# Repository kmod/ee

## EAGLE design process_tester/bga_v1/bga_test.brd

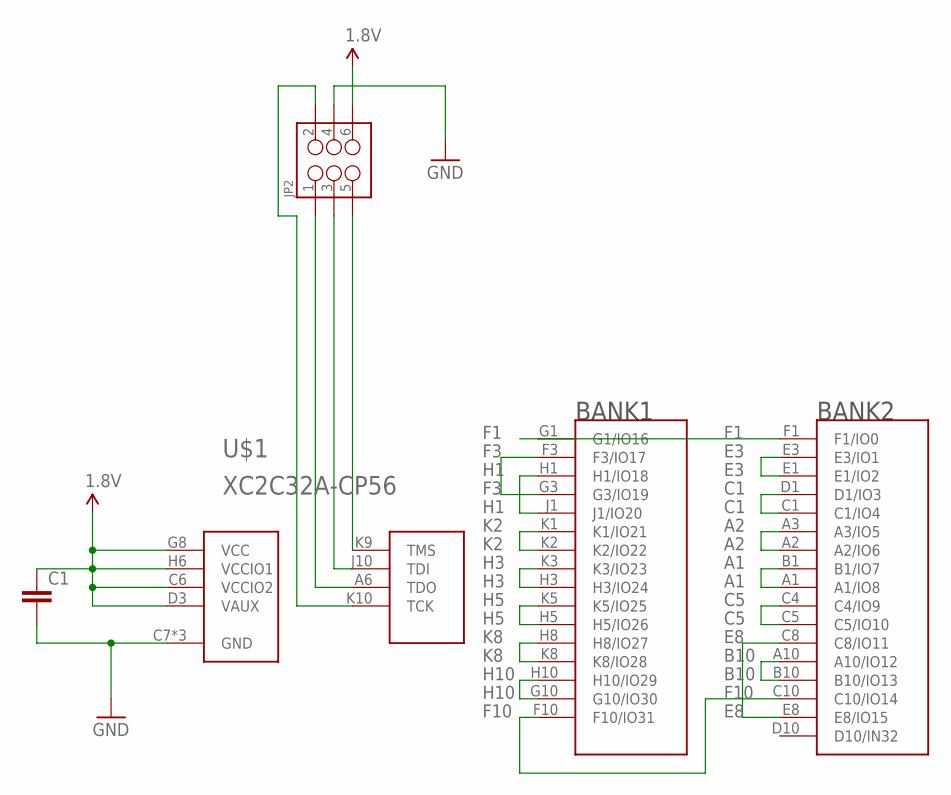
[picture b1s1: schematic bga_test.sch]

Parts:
C1: CAP0402-CAP; 0402-CAP
JP2: M03X2NO_SILK; 2X3-NS
U$1: XC2C32A-CP56; XILINX_CP56

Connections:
1.8V: C1.1, JP2.6, U$1.C6 (VCCIO2), U$1.D3 (VAUX), U$1.G8 (VCC), U$1.H6 (VCCIO1)
A1: U$1.A1 (A1/IO8), U$1.B1 (B1/IO7)
A2: U$1.A2 (A2/IO6), U$1.A3 (A3/IO5)
B10: U$1.A10 (A10/IO12), U$1.B10 (B10/IO13)
C1: U$1.C1 (C1/IO4), U$1.D1 (D1/IO3)
C5: U$1.C4 (C4/IO9), U$1.C5 (C5/IO10)
E3: U$1.E1 (E1/IO2), U$1.E3 (E3/IO1)
E8: U$1.C8 (C8/IO11), U$1.E8 (E8/IO15)
F1: U$1.F1 (F1/IO0), U$1.G1 (G1/IO16)
F3: U$1.F3 (F3/IO17), U$1.G3 (G3/IO19)
F10: U$1.C10 (C10/IO14), U$1.F10 (F10/IO31)
GND: C1.2, JP2.4, U$1.C7 (GND), U$1.F8 (GND), U$1.H4 (GND)
H1: U$1.H1 (H1/IO18), U$1.J1 (J1/IO20)
H3: U$1.H3 (H3/IO24), U$1.K3 (K3/IO23)
H5: U$1.H5 (H5/IO26), U$1.K5 (K5/IO25)
H10: U$1.G10 (G10/IO30), U$1.H10 (H10/IO29)
K2: U$1.K1 (K1/IO21), U$1.K2 (K2/IO22)
K8: U$1.H8 (H8/IO27), U$1.K8 (K8/IO28)
TCK: JP2.2, U$1.K10 (TCK)
TDI: JP2.3, U$1.J10 (TDI)
TDO: JP2.1, U$1.A6 (TDO)
TMS: JP2.5, U$1.K9 (TMS)

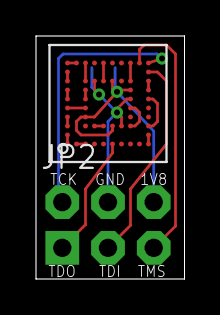
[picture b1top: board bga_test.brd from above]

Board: 2 copper layers, 8.2 x 13.5 mm, 3 parts (1 on the bottom side), 22 nets.

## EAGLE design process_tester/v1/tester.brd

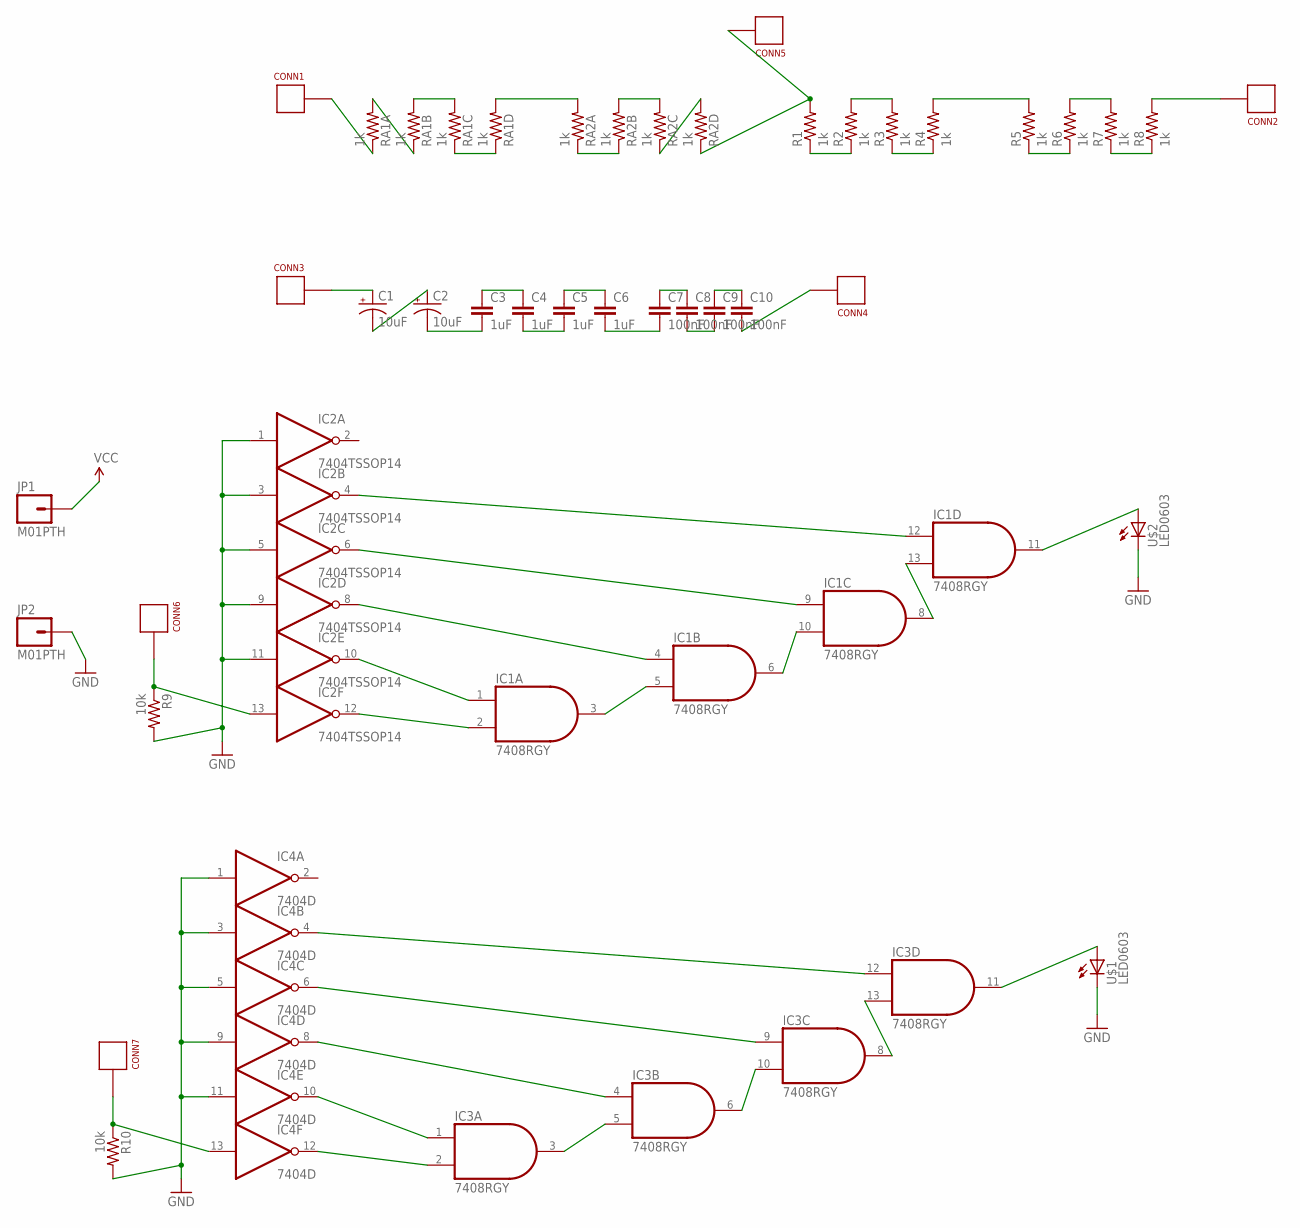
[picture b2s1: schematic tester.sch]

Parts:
C1, C2: 10uF; EIA3216
C3, C4, C5, C6: 1uF; 0805
C7, C8, C9, C10: 100nF; 0402-CAP
CONN1, CONN2, CONN3, CONN4, CONN5, CONN6, CONN7: CONNECTOR; TESTPAD
IC1, IC3: 7408RGY; QFN14
IC2: 7404TSSOP14; TSSOP14
IC4: 7404D; SO14
JP1, JP2: M01PTH; 1X01
R1, R2, R3, R4: 1k; 0603-RES
R5, R6, R7, R8: 1k; 0402-RES
R9, R10: 10k; 0402-RES
RA1, RA2: 1k; 0603-ARV
U$1, U$2: LED0603; 0603_LED

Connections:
GND: IC1.7 (GND), IC2.1 (I), IC2.3 (I), IC2.5 (I), IC2.7 (GND), IC2.9 (I), IC2.11 (I), IC3.7 (GND), IC4.1 (I), IC4.3 (I), IC4.5 (I), IC4.7 (GND), IC4.9 (I), IC4.11 (I), JP2.1, R9.2, R10.2, U$1.C, U$2.C
unnamed: RA1.2 (1), RA1.8 (2)
unnamed: CONN1.P, RA1.1
unnamed: RA1.6 (2), RA1.7 (2)
unnamed: RA1.3 (1), RA1.4 (1)
unnamed: RA1.5 (2), RA2.8 (2)
unnamed: RA2.1, RA2.2 (1)
unnamed: RA2.6 (2), RA2.7 (2)
unnamed: RA2.3 (1), RA2.5 (2)
unnamed: R1.1, R2.1
unnamed: R2.2, R3.2
unnamed: R3.1, R4.1
unnamed: R4.2, R5.2
unnamed: R5.1, R6.1
unnamed: R6.2, R7.2
unnamed: R7.1, R8.1
unnamed: CONN2.P, R8.2
unnamed: CONN5.P, R1.2, RA2.4 (1)
unnamed: C1.A (+), CONN3.P
unnamed: C1.C (-), C2.A (+)
unnamed: C2.C (-), C3.2
unnamed: C3.1, C4.1
unnamed: C4.2, C5.2
unnamed: C5.1, C6.1
unnamed: C6.2, C7.2
unnamed: C8.2, C9.2
unnamed: C9.1, C10.1
unnamed: C7.1, C8.1
unnamed: C10.2, CONN4.P
unnamed: IC1.2 (I1), IC2.12 (O)
unnamed: IC1.1 (I0), IC2.10 (O)
unnamed: IC1.4 (I0), IC2.8 (O)
unnamed: IC1.3 (O), IC1.5 (I1)
unnamed: IC1.6 (O), IC1.10 (I1)
unnamed: IC1.9 (I0), IC2.6 (O)
unnamed: IC1.12 (I0), IC2.4 (O)
unnamed: IC1.8 (O), IC1.13 (I1)
unnamed: IC1.11 (O), U$2.A
unnamed: IC3.3 (O), IC3.5 (I1)
unnamed: IC3.6 (O), IC3.10 (I1)
unnamed: IC3.8 (O), IC3.13 (I1)
unnamed: IC3.11 (O), U$1.A
unnamed: IC3.2 (I1), IC4.12 (O)
unnamed: IC3.1 (I0), IC4.10 (O)
unnamed: IC3.9 (I0), IC4.6 (O)
unnamed: IC3.4 (I0), IC4.8 (O)
unnamed: IC3.12 (I0), IC4.4 (O)
unnamed: CONN6.P, IC2.13 (I), R9.1
unnamed: CONN7.P, IC4.13 (I), R10.1
VCC: IC1.14 (VCC), IC2.14 (VCC), IC3.14 (VCC), IC4.14 (VCC), JP1.1

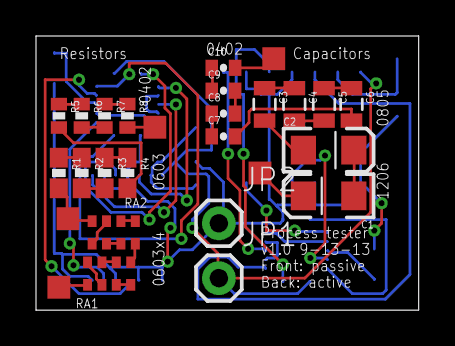
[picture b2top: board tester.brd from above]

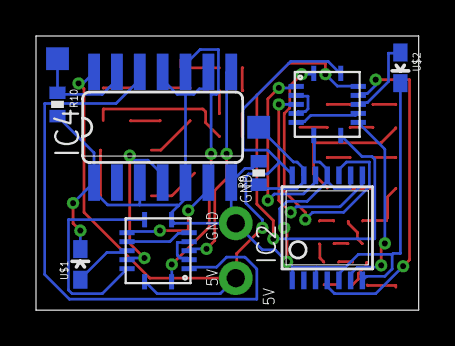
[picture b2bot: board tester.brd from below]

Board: 2 copper layers, 21.3 x 15.2 mm, 37 parts (10 on the bottom side), 50 nets.

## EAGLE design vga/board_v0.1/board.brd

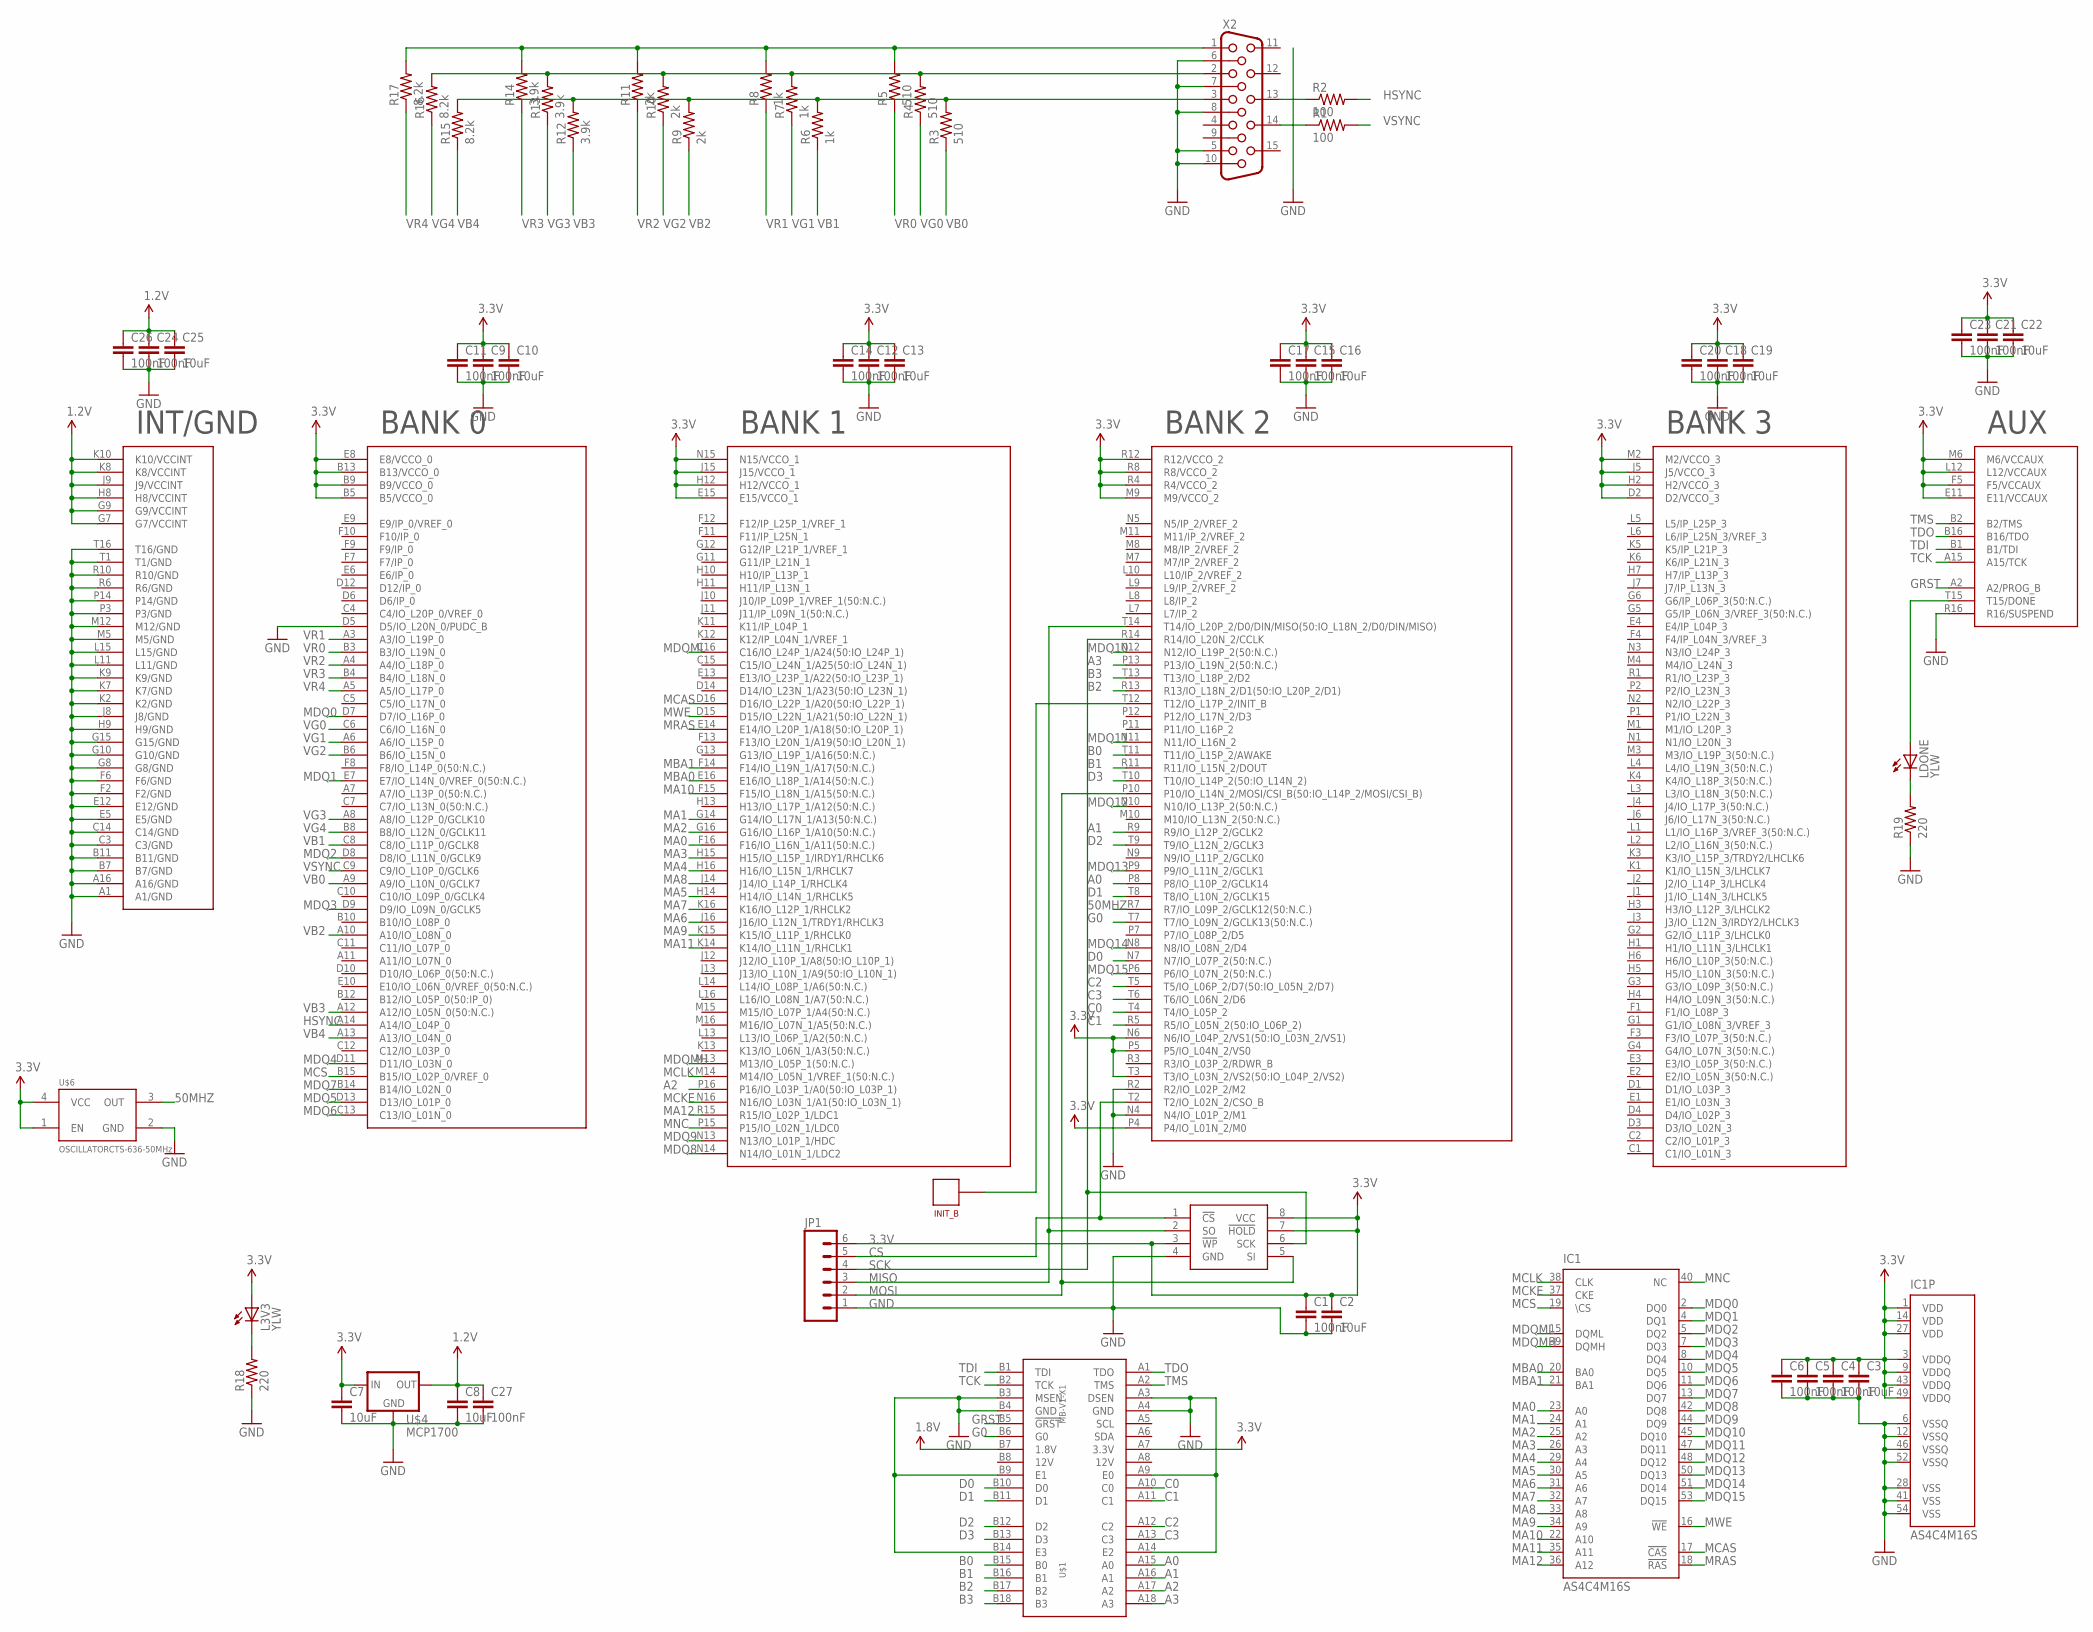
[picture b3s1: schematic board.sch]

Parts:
C1, C4, C5, C6, C9, C11, C12, C14, C15, C17, C18, C20, C21, C23, C24, C26, C27: 100nF; 0402-CAP
C2, C3, C7, C8, C10, C13, C16, C19, C22, C25: 10uF; 0805
IC1: AS4C4M16S; TSOP54-400
INIT_B: CONNECTOR1.27; TESTPAD-1.27
JP1: M06SIP; 1X06
L3V3: YLW; 0603_LED
LDONE: YLW; 0603_LED
R1, R2: 100; 0603-RES
R3, R4, R5: 510; 0603-RES
R6, R7, R8: 1k; 0603-RES
R9, R10, R11: 2k; 0603-RES
R12, R13, R14: 3.9k; 0603-RES
R15, R16, R17: 8.2k; 0603-RES
R18, R19: 220; 0603-RES
U$1: MB-V1-X1; PCIE-X1-EDGE
U$2: XC3S{50,100,200}A-FT256; XILINX_FT256
U$4: MCP1700; SOT23-3
U$6: OSCILLATORCTS-636-50MHz; CTS-636
U$7: S25FL; SO08
X2: HF15H; HDF15H

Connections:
1.2V: C8.1, C24.1, C25.1, C26.1, C27.1, U$2.G7 (G7/VCCINT), U$2.G9 (G9/VCCINT), U$2.H8 (H8/VCCINT), U$2.J9 (J9/VCCINT), U$2.K8 (K8/VCCINT), U$2.K10 (K10/VCCINT), U$4.2 (OUT)
1.8V: U$1.B7 (1.8V)
3.3V: C1.1, C2.1, C3.1, C4.1, C5.1, C6.1, C7.1, C9.1, C10.1, C11.1, C12.1, C13.1, C14.1, C15.1, C16.1, C17.1, C18.1, C19.1, C20.1, C21.1, C22.1, C23.1, IC1.1 (VDD), IC1.3 (VDDQ), IC1.9 (VDDQ), IC1.14 (VDD), IC1.27 (VDD), IC1.43 (VDDQ), IC1.49 (VDDQ), JP1.6, L3V3.A, U$1.A7 (3.3V), U$2.B5 (B5/VCCO_0), U$2.B9 (B9/VCCO_0), U$2.B13 (B13/VCCO_0), U$2.D2 (D2/VCCO_3), U$2.E8 (E8/VCCO_0), U$2.E11 (E11/VCCAUX), U$2.E15 (E15/VCCO_1), U$2.F5 (F5/VCCAUX), U$2.H2 (H2/VCCO_3), U$2.H12 (H12/VCCO_1), U$2.J5 (J5/VCCO_3), U$2.J15 (J15/VCCO_1), U$2.L12 (L12/VCCAUX), U$2.M2 (M2/VCCO_3), U$2.M6 (M6/VCCAUX), U$2.M9 (M9/VCCO_2), U$2.N6 (N6/IO_L04P_2/VS1(50:IO_L03N_2/VS1)), U$2.N15 (N15/VCCO_1), U$2.P4 (P4/IO_L01N_2/M0), U$2.P5 (P5/IO_L04N_2/VS0), U$2.R4 (R4/VCCO_2), U$2.R8 (R8/VCCO_2), U$2.R12 (R12/VCCO_2), U$2.T3 (T3/IO_L03N_2/VS2(50:IO_L04P_2/VS2)), U$4.3 (IN), U$6.1 (EN), U$6.4 (VCC), U$7.3 (!WP), U$7.7 (!HOLD), U$7.8 (VCC)
50MHZ: U$2.R7 (R7/IO_L09P_2/GCLK12(50:N.C.)), U$6.3 (OUT)
A0: U$1.A15 (A0), U$2.P8 (P8/IO_L10P_2/GCLK14)
A1: U$1.A16 (A1), U$2.R9 (R9/IO_L12P_2/GCLK2)
A2: U$1.A17 (A2), U$2.P16 (P16/IO_L03P_1/A0(50:IO_L03P_1))
A3: U$1.A18 (A3), U$2.P13 (P13/IO_L19N_2(50:N.C.))
B0: U$1.B15 (B0), U$2.T11 (T11/IO_L15P_2/AWAKE)
B1: U$1.B16 (B1), U$2.R11 (R11/IO_L15N_2/DOUT)
B2: U$1.B17 (B2), U$2.R13 (R13/IO_L18N_2/D1(50:IO_L20P_2/D1))
B3: U$1.B18 (B3), U$2.T13 (T13/IO_L18P_2/D2)
C0: U$1.A10 (C0), U$2.T4 (T4/IO_L05P_2)
C1: U$1.A11 (C1), U$2.R5 (R5/IO_L05N_2(50:IO_L06P_2))
C2: U$1.A12 (C2), U$2.T5 (T5/IO_L06P_2/D7(50:IO_L05N_2/D7))
C3: U$1.A13 (C3), U$2.T6 (T6/IO_L06N_2/D6)
CS: JP1.5, U$2.T2 (T2/IO_L02N_2/CSO_B), U$7.1 (!CS)
D0: U$1.B10 (D0), U$2.N7 (N7/IO_L07P_2(50:N.C.))
D1: U$1.B11 (D1), U$2.T8 (T8/IO_L10N_2/GCLK15)
D2: U$1.B12 (D2), U$2.T9 (T9/IO_L12N_2/GCLK3)
D3: U$1.B13 (D3), U$2.T10 (T10/IO_L14P_2(50:IO_L14N_2))
DONE: LDONE.A, U$2.T15 (T15/DONE)
G0: U$1.B6 (G0), U$2.T7 (T7/IO_L09N_2/GCLK13(50:N.C.))
GND: C1.2, C2.2, C3.2, C4.2, C5.2, C6.2, C7.2, C8.2, C9.2, C10.2, C11.2, C12.2, C13.2, C14.2, C15.2, C16.2, C17.2, C18.2, C19.2, C20.2, C21.2, C22.2, C23.2, C24.2, C25.2, C26.2, C27.2, IC1.6 (VSSQ), IC1.12 (VSSQ), IC1.28 (VSS), IC1.41 (VSS), IC1.46 (VSSQ), IC1.52 (VSSQ), IC1.54 (VSS), JP1.1, R18.1, R19.1, U$1.A3 (DSEN), U$1.A4 (GND), U$1.A9 (E0), U$1.A14 (E2), U$1.B3 (MSEN), U$1.B4 (GND), U$1.B9 (E1), U$1.B14 (E3), U$2.A1 (A1/GND), U$2.A16 (A16/GND), U$2.B7 (B7/GND), U$2.B11 (B11/GND), U$2.C3 (C3/GND), U$2.C14 (C14/GND), U$2.D5 (D5/IO_L20N_0/PUDC_B), U$2.E5 (E5/GND), U$2.E12 (E12/GND), U$2.F2 (F2/GND), U$2.F6 (F6/GND), U$2.G8 (G8/GND), U$2.G10 (G10/GND), U$2.G15 (G15/GND), U$2.H9 (H9/GND), U$2.J8 (J8/GND), U$2.K2 (K2/GND), U$2.K7 (K7/GND), U$2.K9 (K9/GND), U$2.L11 (L11/GND), U$2.L15 (L15/GND), U$2.M5 (M5/GND), U$2.M12 (M12/GND), U$2.N4 (N4/IO_L01P_2/M1), U$2.P3 (P3/GND), U$2.P14 (P14/GND), U$2.R2 (R2/IO_L02P_2/M2), U$2.R6 (R6/GND), U$2.R10 (R10/GND), U$2.R16 (R16/SUSPEND), U$2.T1 (T1/GND), U$2.T16 (T16/GND), U$4.1 (GND), U$6.2 (GND), U$7.4 (GND), X2.5, X2.6, X2.7, X2.8, X2.10
GRST: U$1.B5 (!GRST), U$2.A2 (A2/PROG_B)
HSYNC: R2.2, U$2.A14 (A14/IO_L04P_0)
MA0: IC1.23 (A0), U$2.F16 (F16/IO_L16N_1/A11(50:N.C.))
MA1: IC1.24 (A1), U$2.G14 (G14/IO_L17N_1/A13(50:N.C.))
MA2: IC1.25 (A2), U$2.G16 (G16/IO_L16P_1/A10(50:N.C.))
MA3: IC1.26 (A3), U$2.H15 (H15/IO_L15P_1/IRDY1/RHCLK6)
MA4: IC1.29 (A4), U$2.H16 (H16/IO_L15N_1/RHCLK7)
MA5: IC1.30 (A5), U$2.H14 (H14/IO_L14N_1/RHCLK5)
MA6: IC1.31 (A6), U$2.J16 (J16/IO_L12N_1/TRDY1/RHCLK3)
MA7: IC1.32 (A7), U$2.K16 (K16/IO_L12P_1/RHCLK2)
MA8: IC1.33 (A8), U$2.J14 (J14/IO_L14P_1/RHCLK4)
MA9: IC1.34 (A9), U$2.K15 (K15/IO_L11P_1/RHCLK0)
MA10: IC1.22 (A10), U$2.F15 (F15/IO_L18N_1/A15(50:N.C.))
MA11: IC1.35 (A11), U$2.K14 (K14/IO_L11N_1/RHCLK1)
MA12: IC1.36 (A12), U$2.R15 (R15/IO_L02P_1/LDC1)
MBA0: IC1.20 (BA0), U$2.E16 (E16/IO_L18P_1/A14(50:N.C.))
MBA1: IC1.21 (BA1), U$2.F14 (F14/IO_L19N_1/A17(50:N.C.))
MCAS: IC1.17 (!CAS), U$2.D16 (D16/IO_L22P_1/A20(50:IO_L22P_1))
MCKE: IC1.37 (CKE), U$2.N16 (N16/IO_L03N_1/A1(50:IO_L03N_1))
MCLK: IC1.38 (CLK), U$2.M14 (M14/IO_L05N_1/VREF_1(50:N.C.))
MCS: IC1.19 (\CS), U$2.B15 (B15/IO_L02P_0/VREF_0)
MDQ0: IC1.2 (DQ0), U$2.D7 (D7/IO_L16P_0)
MDQ1: IC1.4 (DQ1), U$2.E7 (E7/IO_L14N_0/VREF_0(50:N.C.))
MDQ2: IC1.5 (DQ2), U$2.D8 (D8/IO_L11N_0/GCLK9)
MDQ3: IC1.7 (DQ3), U$2.D9 (D9/IO_L09N_0/GCLK5)
MDQ4: IC1.8 (DQ4), U$2.D11 (D11/IO_L03N_0)
MDQ5: IC1.10 (DQ5), U$2.D13 (D13/IO_L01P_0)
MDQ6: IC1.11 (DQ6), U$2.C13 (C13/IO_L01N_0)
MDQ7: IC1.13 (DQ7), U$2.B14 (B14/IO_L02N_0)
MDQ8: IC1.42 (DQ8), U$2.N14 (N14/IO_L01N_1/LDC2)
MDQ9: IC1.44 (DQ9), U$2.N13 (N13/IO_L01P_1/HDC)
MDQ10: IC1.45 (DQ10), U$2.N12 (N12/IO_L19P_2(50:N.C.))
MDQ11: IC1.47 (DQ11), U$2.N11 (N11/IO_L16N_2)
MDQ12: IC1.48 (DQ12), U$2.N10 (N10/IO_L13P_2(50:N.C.))
MDQ13: IC1.50 (DQ13), U$2.P9 (P9/IO_L11N_2/GCLK1)
MDQ14: IC1.51 (DQ14), U$2.N8 (N8/IO_L08N_2/D4)
MDQ15: IC1.53 (DQ15), U$2.P6 (P6/IO_L07N_2(50:N.C.))
MDQMH: IC1.39 (DQMH), U$2.M13 (M13/IO_L05P_1(50:N.C.))
MDQML: IC1.15 (DQML), U$2.C16 (C16/IO_L24P_1/A24(50:IO_L24P_1))
MISO: JP1.3, U$2.T14 (T14/IO_L20P_2/D0/DIN/MISO(50:IO_L18N_2/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), U$7.2 (SO)
MNC: IC1.40 (NC), U$2.P15 (P15/IO_L02N_1/LDC0)
MOSI: JP1.2, U$2.P10 (P10/IO_L14N_2/MOSI/CSI_B(50:IO_L14P_2/M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), U$7.5 (SI)
MRAS: IC1.18 (!RAS), U$2.E14 (E14/IO_L20P_1/A18(50:IO_L20P_1))
MWE: IC1.16 (!WE), U$2.D15 (D15/IO_L22N_1/A21(50:IO_L22N_1))
unnamed: R1.1, X2.14
unnamed: R2.1, X2.13
unnamed: LDONE.C, R19.2
unnamed: INIT_B.P, U$2.T12 (T12/IO_L17P_2/INIT_B)
unnamed: R3.2, R6.2, R9.2, R12.2, R15.2, X2.3
unnamed: L3V3.C, R18.2
unnamed: R4.2, R7.2, R10.2, R13.2, R16.2, X2.2
unnamed: R5.2, R8.2, R11.2, R14.2, R17.2, X2.1
SCK: JP1.4, U$2.R14 (R14/IO_L20N_2/CCLK), U$7.6 (SCK)
TCK: U$1.B2 (TCK), U$2.A15 (A15/TCK)
TDI: U$1.B1 (TDI), U$2.B1 (B1/TDI)
TDO: U$1.A1 (TDO), U$2.B16 (B16/TDO)
TMS: U$1.A2 (TMS), U$2.B2 (B2/TMS)
VB0: R3.1, U$2.A9 (A9/IO_L10N_0/GCLK7)
VB1: R6.1, U$2.C8 (C8/IO_L11P_0/GCLK8)
VB2: R9.1, U$2.A10 (A10/IO_L08N_0)
VB3: R12.1, U$2.A12 (A12/IO_L05N_0(50:N.C.))
VB4: R15.1, U$2.A13 (A13/IO_L04N_0)
VG0: R4.1, U$2.C6 (C6/IO_L16N_0)
VG1: R7.1, U$2.A6 (A6/IO_L15P_0)
VG2: R10.1, U$2.B6 (B6/IO_L15N_0)
VG3: R13.1, U$2.A8 (A8/IO_L12P_0/GCLK10)
VG4: R16.1, U$2.B8 (B8/IO_L12N_0/GCLK11)
VR0: R5.1, U$2.B3 (B3/IO_L19N_0)
VR1: R8.1, U$2.A3 (A3/IO_L19P_0)
VR2: R11.1, U$2.A4 (A4/IO_L18P_0)
VR3: R14.1, U$2.B4 (B4/IO_L18N_0)
VR4: R17.1, U$2.A5 (A5/IO_L17P_0)
VSYNC: R1.2, U$2.C9 (C9/IO_L10P_0/GCLK6)

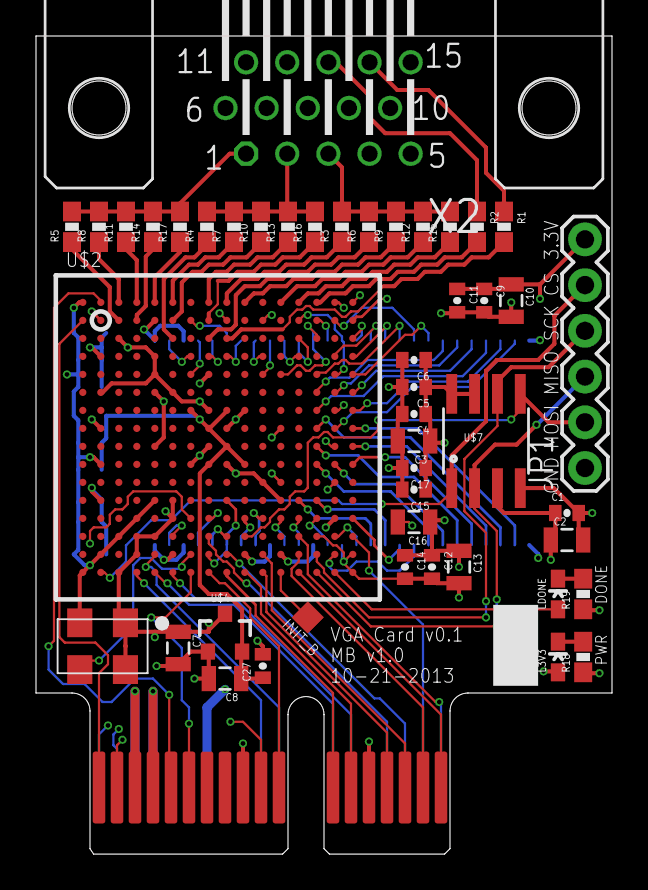
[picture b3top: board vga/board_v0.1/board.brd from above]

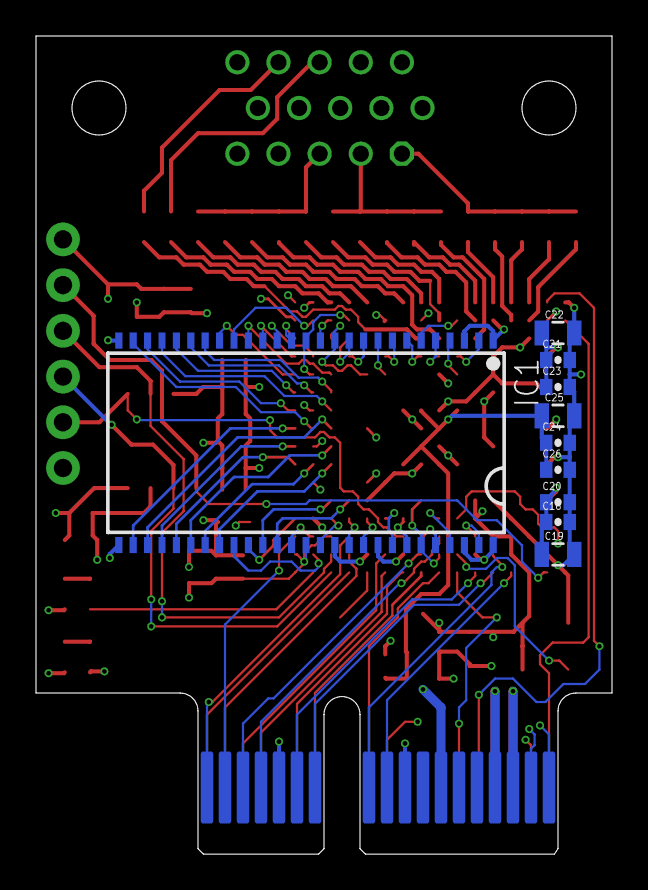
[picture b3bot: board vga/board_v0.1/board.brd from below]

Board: 4 copper layers, 32.0 x 45.5 mm, 57 parts (10 on the bottom side), 96 nets.

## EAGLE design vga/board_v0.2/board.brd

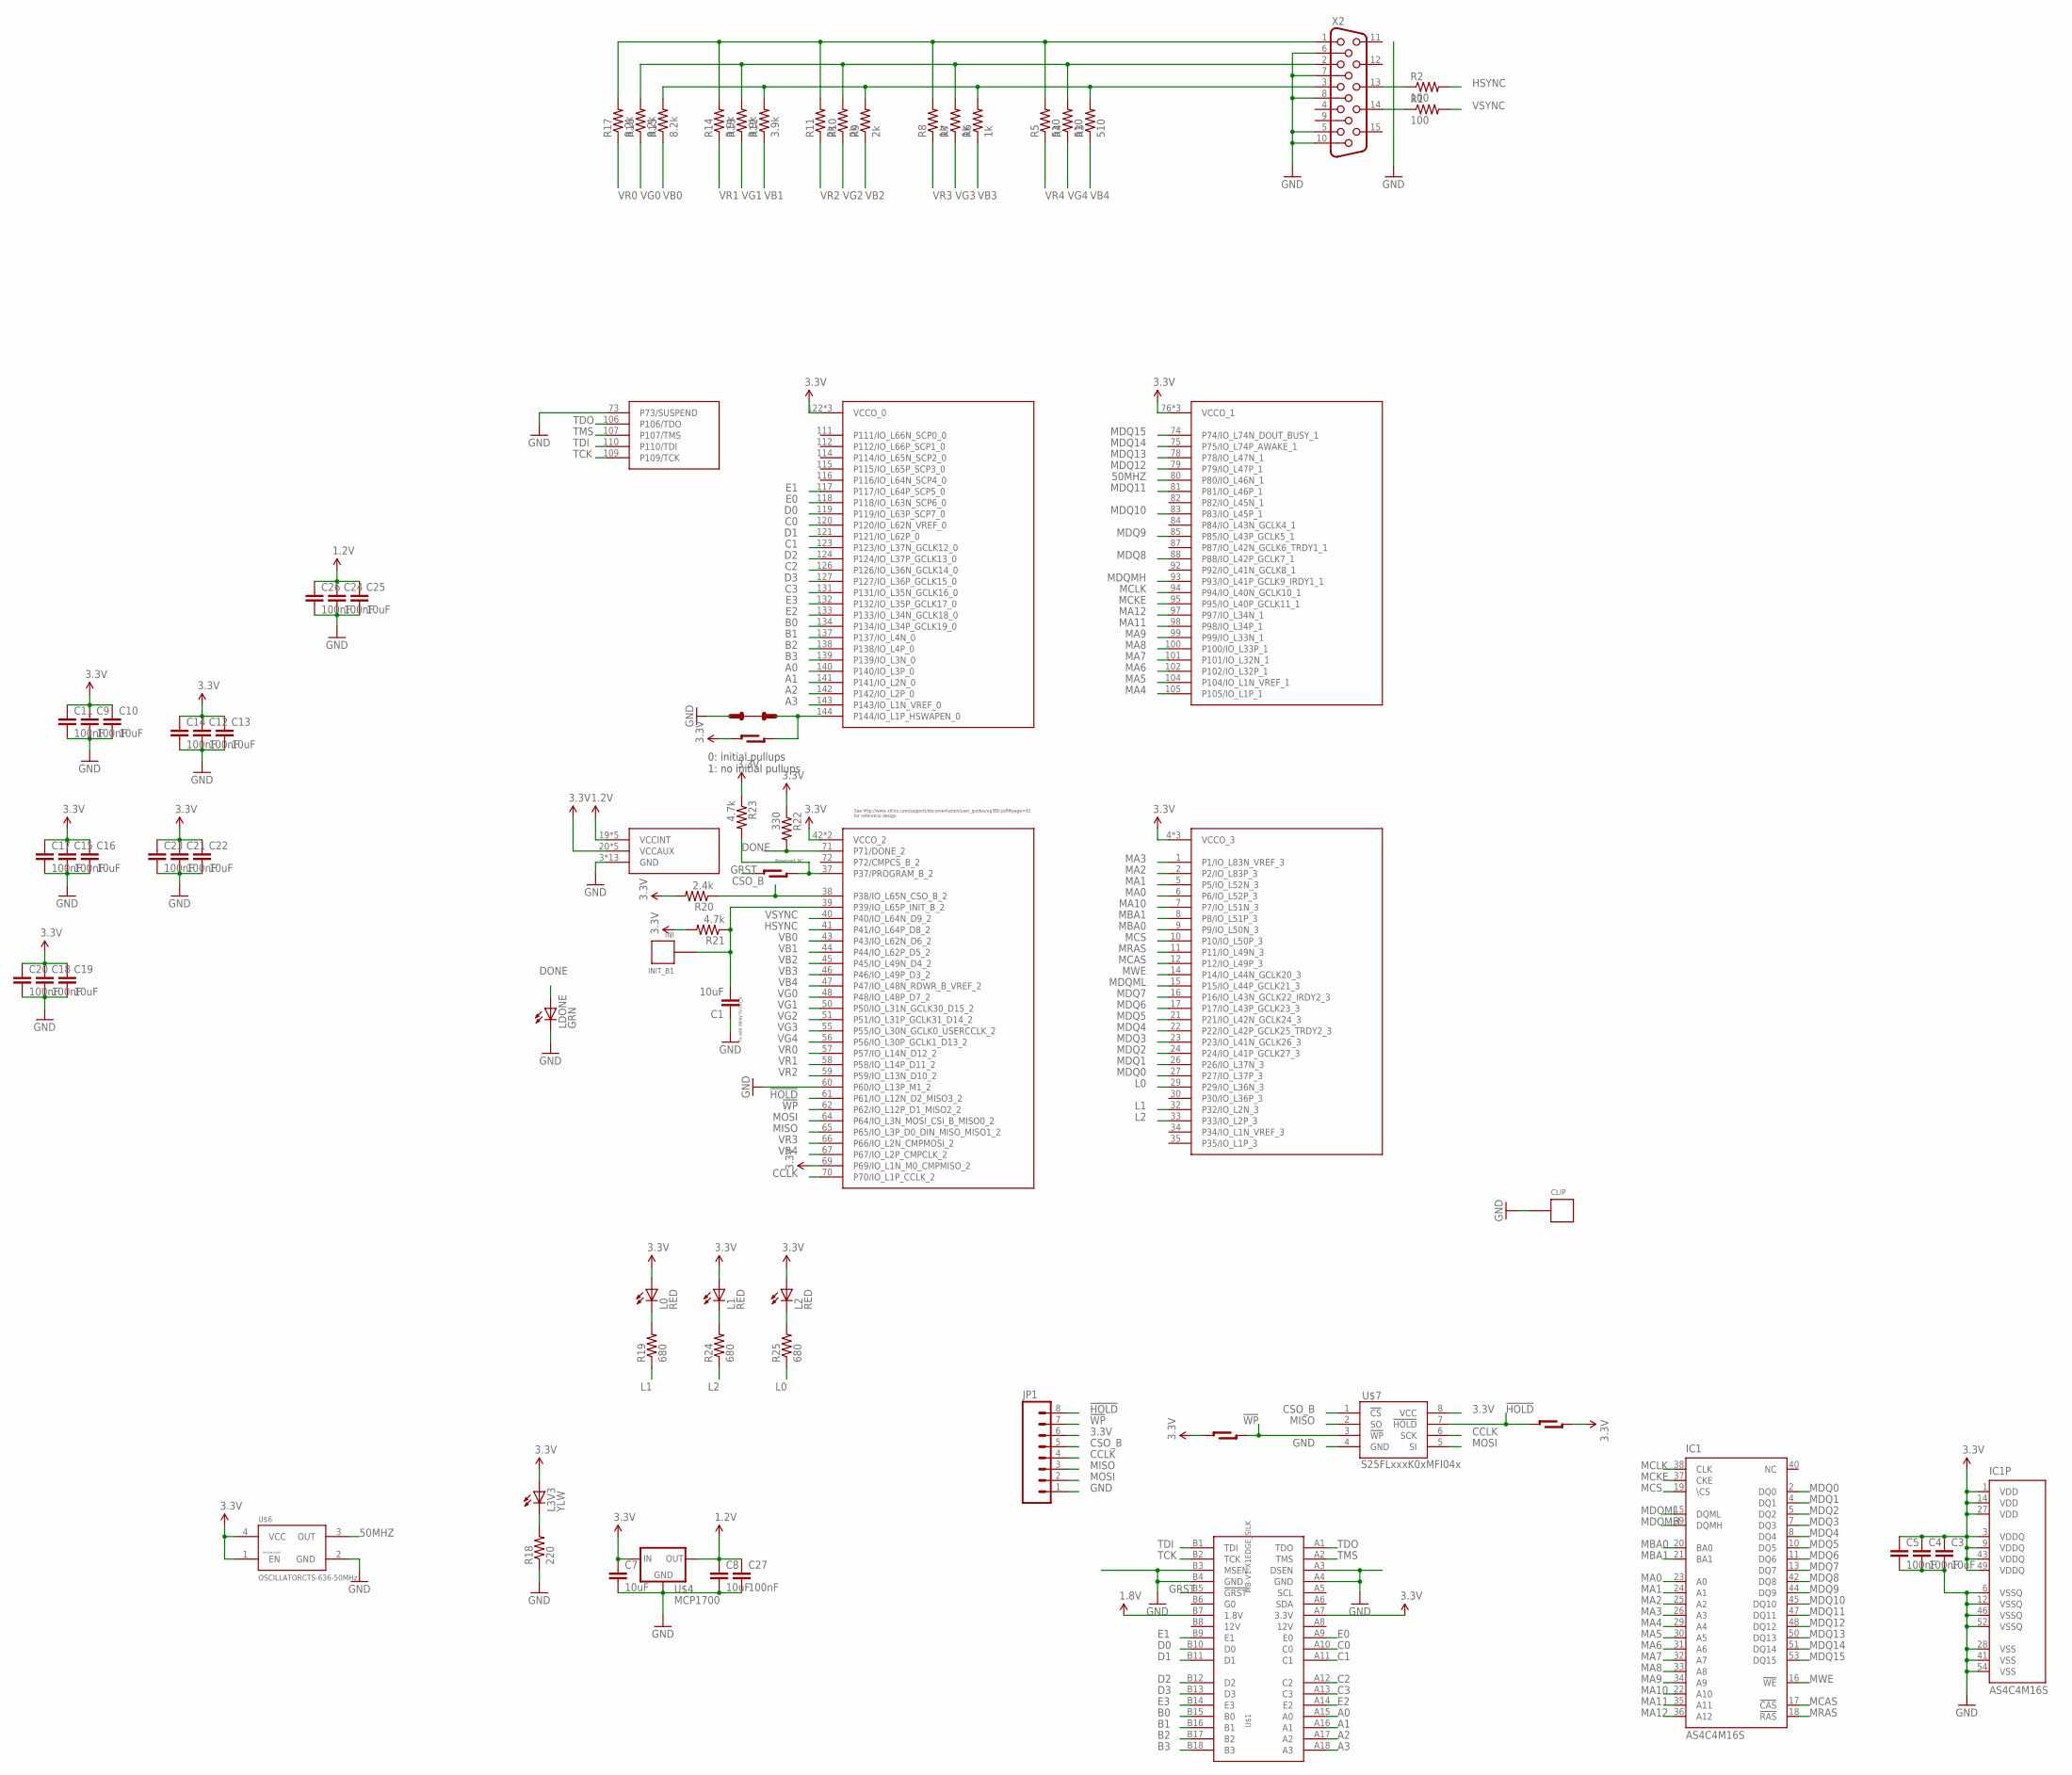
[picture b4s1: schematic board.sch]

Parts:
C1, C3, C7, C8, C10, C13, C16, C19, C22, C25: 10uF; 0805
C4, C5, C9, C11, C12, C14, C15, C17, C18, C20, C21, C23, C24, C26, C27: 100nF; 0402-CAP
CLIP: CONNECTORCLIP; CLIP-AREA
IC1: AS4C4M16S; TSOP54-400
INIT_B1: INI; TESTPAD-1.27
JP1: M08LOCK; 1X08_LOCK
L0, L1, L2: RED; 0603_LED
L3V3: YLW; 0603_LED
LDONE: GRN; 0603_LED
R1, R2: 100; 0603-RES
R3, R4, R5: 510; 0603-RES
R6, R7, R8: 1k; 0603-RES
R9, R10, R11: 2k; 0603-RES
R12, R13, R14: 3.9k; 0603-RES
R15, R16, R17: 8.2k; 0603-RES
R18: 220; 0603-RES
R19, R24, R25: 680; 0603-RES
R20: 2.4k; 0603-RES
R21, R23: 4.7k; 0603-RES
R22: 330; 0603-RES
SB1, SB3, SB4, SB5: SOLDER-BRIDGEOPEN; SOLDER-BRIDGE-OPEN
SB2: TRACE-CUT
U$1: MB-V1-X1EDGE_SILK; MB-V1-X1-EDGE
U$4: MCP1700; SOT23-3
U$6: OSCILLATORCTS-636-50MHz; CTS-636
U$7: S25FLxxxK0xMFI04x; SO08
U$9: XC6SLX-TQ144; XILINX_TQ144
X2: HF15H; HDF15H

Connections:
1.2V: C8.1, C24.1, C25.1, C26.1, C27.1, U$4.2 (OUT), U$9.19 (VCCINT), U$9.28 (VCCINT), U$9.52 (VCCINT), U$9.89 (VCCINT), U$9.128 (VCCINT)
1.8V: U$1.B7 (1.8V)
3.3V: C3.1, C4.1, C5.1, C7.1, C9.1, C10.1, C11.1, C12.1, C13.1, C14.1, C15.1, C16.1, C17.1, C18.1, C19.1, C20.1, C21.1, C22.1, C23.1, IC1.1 (VDD), IC1.3 (VDDQ), IC1.9 (VDDQ), IC1.14 (VDD), IC1.27 (VDD), IC1.43 (VDDQ), IC1.49 (VDDQ), JP1.6, L0.A, L1.A, L2.A, L3V3.A, R20.2, R21.2, R22.1, R23.1, SB1.R1, SB1.R2, SB3.L1, SB3.L2, SB4.R1, SB4.R2, U$1.A7 (3.3V), U$4.3 (IN), U$6.1 (EN), U$6.4 (VCC), U$7.8 (VCC), U$9.4 (VCCO_3), U$9.18 (VCCO_3), U$9.20 (VCCAUX), U$9.31 (VCCO_3), U$9.36 (VCCAUX), U$9.42 (VCCO_2), U$9.53 (VCCAUX), U$9.63 (VCCO_2), U$9.69 (P69/IO_L1N_M0_CMPMISO_2), U$9.76 (VCCO_1), U$9.86 (VCCO_1), U$9.90 (VCCAUX), U$9.103 (VCCO_1), U$9.122 (VCCO_0), U$9.125 (VCCO_0), U$9.129 (VCCAUX), U$9.135 (VCCO_0)
50MHZ: U$6.3 (OUT), U$9.80 (P80/IO_L46N_1)
!HOLD: JP1.8, SB3.R1, SB3.R2, U$7.7 (!HOLD), U$9.61 (P61/IO_L12N_D2_MISO3_2)
!WP: JP1.7, SB4.L1, SB4.L2, U$7.3 (!WP), U$9.62 (P62/IO_L12P_D1_MISO2_2)
A0: U$1.A15 (A0), U$9.140 (P140/IO_L3P_0)
A1: U$1.A16 (A1), U$9.141 (P141/IO_L2N_0)
A2: U$1.A17 (A2), U$9.142 (P142/IO_L2P_0)
A3: U$1.A18 (A3), U$9.143 (P143/IO_L1N_VREF_0)
B0: U$1.B15 (B0), U$9.134 (P134/IO_L34P_GCLK19_0)
B1: U$1.B16 (B1), U$9.137 (P137/IO_L4N_0)
B2: U$1.B17 (B2), U$9.138 (P138/IO_L4P_0)
B3: U$1.B18 (B3), U$9.139 (P139/IO_L3N_0)
C0: U$1.A10 (C0), U$9.120 (P120/IO_L62N_VREF_0)
C1: U$1.A11 (C1), U$9.123 (P123/IO_L37N_GCLK12_0)
C2: U$1.A12 (C2), U$9.126 (P126/IO_L36N_GCLK14_0)
C3: U$1.A13 (C3), U$9.131 (P131/IO_L35N_GCLK16_0)
CCLK: JP1.4, U$7.6 (SCK), U$9.70 (P70/IO_L1P_CCLK_2)
CSO_B: JP1.5, R20.1, U$7.1 (!CS), U$9.38 (P38/IO_L65N_CSO_B_2)
D0: U$1.B10 (D0), U$9.119 (P119/IO_L63P_SCP7_0)
D1: U$1.B11 (D1), U$9.121 (P121/IO_L62P_0)
D2: U$1.B12 (D2), U$9.124 (P124/IO_L37P_GCLK13_0)
D3: U$1.B13 (D3), U$9.127 (P127/IO_L36P_GCLK15_0)
DONE: LDONE.A, R22.2, U$9.71 (P71/DONE_2)
E0: U$1.A9 (E0), U$9.118 (P118/IO_L63N_SCP6_0)
E1: U$1.B9 (E1), U$9.117 (P117/IO_L64P_SCP5_0)
E2: U$1.A14 (E2), U$9.133 (P133/IO_L34N_GCLK18_0)
E3: U$1.B14 (E3), U$9.132 (P132/IO_L35P_GCLK17_0)
GND: C1.1, C3.2, C4.2, C5.2, C7.2, C8.2, C9.2, C10.2, C11.2, C12.2, C13.2, C14.2, C15.2, C16.2, C17.2, C18.2, C19.2, C20.2, C21.2, C22.2, C23.2, C24.2, C25.2, C26.2, C27.2, CLIP.P$1, CLIP.P$2, IC1.6 (VSSQ), IC1.12 (VSSQ), IC1.28 (VSS), IC1.41 (VSS), IC1.46 (VSSQ), IC1.52 (VSSQ), IC1.54 (VSS), JP1.1, LDONE.C, R18.1, SB2.L1, U$1.A3 (DSEN), U$1.A4 (GND), U$1.B3 (MSEN), U$1.B4 (GND), U$4.1 (GND), U$6.2 (GND), U$7.4 (GND), U$9.3 (GND), U$9.13 (GND), U$9.25 (GND), U$9.49 (GND), U$9.54 (GND), U$9.60 (P60/IO_L13P_M1_2), U$9.68 (GND), U$9.73 (P73/SUSPEND), U$9.77 (GND), U$9.91 (GND), U$9.96 (GND), U$9.108 (GND), U$9.113 (GND), U$9.130 (GND), U$9.136 (GND), X2.5, X2.6, X2.7, X2.8, X2.10
GRST: SB5.L1, SB5.L2, U$1.B5 (!GRST)
HSWAPEN: SB1.L1, SB1.L2, SB2.R1, U$9.144 (P144/IO_L1P_HSWAPEN_0)
HSYNC: R2.2, U$9.41 (P41/IO_L64P_D8_2)
INIT_B: C1.2, INIT_B1.P, R21.1, U$9.39 (P39/IO_L65P_INIT_B_2)
L0: R25.1, U$9.29 (P29/IO_L36N_3)
L1: R19.1, U$9.32 (P32/IO_L2N_3)
L2: R24.1, U$9.33 (P33/IO_L2P_3)
MA0: IC1.23 (A0), U$9.6 (P6/IO_L52P_3)
MA1: IC1.24 (A1), U$9.5 (P5/IO_L52N_3)
MA2: IC1.25 (A2), U$9.2 (P2/IO_L83P_3)
MA3: IC1.26 (A3), U$9.1 (P1/IO_L83N_VREF_3)
MA4: IC1.29 (A4), U$9.105 (P105/IO_L1P_1)
MA5: IC1.30 (A5), U$9.104 (P104/IO_L1N_VREF_1)
MA6: IC1.31 (A6), U$9.102 (P102/IO_L32P_1)
MA7: IC1.32 (A7), U$9.101 (P101/IO_L32N_1)
MA8: IC1.33 (A8), U$9.100 (P100/IO_L33P_1)
MA9: IC1.34 (A9), U$9.99 (P99/IO_L33N_1)
MA10: IC1.22 (A10), U$9.7 (P7/IO_L51N_3)
MA11: IC1.35 (A11), U$9.98 (P98/IO_L34P_1)
MA12: IC1.36 (A12), U$9.97 (P97/IO_L34N_1)
MBA0: IC1.20 (BA0), U$9.9 (P9/IO_L50N_3)
MBA1: IC1.21 (BA1), U$9.8 (P8/IO_L51P_3)
MCAS: IC1.17 (!CAS), U$9.12 (P12/IO_L49P_3)
MCKE: IC1.37 (CKE), U$9.95 (P95/IO_L40P_GCLK11_1)
MCLK: IC1.38 (CLK), U$9.94 (P94/IO_L40N_GCLK10_1)
MCS: IC1.19 (\CS), U$9.10 (P10/IO_L50P_3)
MDQ0: IC1.2 (DQ0), U$9.27 (P27/IO_L37P_3)
MDQ1: IC1.4 (DQ1), U$9.26 (P26/IO_L37N_3)
MDQ2: IC1.5 (DQ2), U$9.24 (P24/IO_L41P_GCLK27_3)
MDQ3: IC1.7 (DQ3), U$9.23 (P23/IO_L41N_GCLK26_3)
MDQ4: IC1.8 (DQ4), U$9.22 (P22/IO_L42P_GCLK25_TRDY2_3)
MDQ5: IC1.10 (DQ5), U$9.21 (P21/IO_L42N_GCLK24_3)
MDQ6: IC1.11 (DQ6), U$9.17 (P17/IO_L43P_GCLK23_3)
MDQ7: IC1.13 (DQ7), U$9.16 (P16/IO_L43N_GCLK22_IRDY2_3)
MDQ8: IC1.42 (DQ8), U$9.88 (P88/IO_L42P_GCLK7_1)
MDQ9: IC1.44 (DQ9), U$9.85 (P85/IO_L43P_GCLK5_1)
MDQ10: IC1.45 (DQ10), U$9.83 (P83/IO_L45P_1)
MDQ11: IC1.47 (DQ11), U$9.81 (P81/IO_L46P_1)
MDQ12: IC1.48 (DQ12), U$9.79 (P79/IO_L47P_1)
MDQ13: IC1.50 (DQ13), U$9.78 (P78/IO_L47N_1)
MDQ14: IC1.51 (DQ14), U$9.75 (P75/IO_L74P_AWAKE_1)
MDQ15: IC1.53 (DQ15), U$9.74 (P74/IO_L74N_DOUT_BUSY_1)
MDQMH: IC1.39 (DQMH), U$9.93 (P93/IO_L41P_GCLK9_IRDY1_1)
MDQML: IC1.15 (DQML), U$9.15 (P15/IO_L44P_GCLK21_3)
MISO: JP1.3, U$7.2 (SO), U$9.65 (P65/IO_L3P_D0_DIN_MISO_MISO1_2)
MOSI: JP1.2, U$7.5 (SI), U$9.64 (P64/IO_L3N_MOSI_CSI_B_MISO0_2)
MRAS: IC1.18 (!RAS), U$9.11 (P11/IO_L49N_3)
MWE: IC1.16 (!WE), U$9.14 (P14/IO_L44N_GCLK20_3)
unnamed: R1.1, X2.14
unnamed: R2.1, X2.13
unnamed: L0.C, R19.2
unnamed: L1.C, R24.2
unnamed: R3.2, R6.2, R9.2, R12.2, R15.2, X2.3
unnamed: L3V3.C, R18.2
unnamed: R4.2, R7.2, R10.2, R13.2, R16.2, X2.2
unnamed: R5.2, R8.2, R11.2, R14.2, R17.2, X2.1
unnamed: L2.C, R25.2
PROGRAM: R23.2, SB5.R1, SB5.R2, U$9.37 (P37/PROGRAM_B_2)
TCK: U$1.B2 (TCK), U$9.109 (P109/TCK)
TDI: U$1.B1 (TDI), U$9.110 (P110/TDI)
TDO: U$1.A1 (TDO), U$9.106 (P106/TDO)
TMS: U$1.A2 (TMS), U$9.107 (P107/TMS)
VB0: R15.1, U$9.43 (P43/IO_L62N_D6_2)
VB1: R12.1, U$9.44 (P44/IO_L62P_D5_2)
VB2: R9.1, U$9.45 (P45/IO_L49N_D4_2)
VB3: R6.1, U$9.46 (P46/IO_L49P_D3_2)
VB4: R3.1, U$9.47 (P47/IO_L48N_RDWR_B_VREF_2)
VG0: R16.1, U$9.48 (P48/IO_L48P_D7_2)
VG1: R13.1, U$9.50 (P50/IO_L31N_GCLK30_D15_2)
VG2: R10.1, U$9.51 (P51/IO_L31P_GCLK31_D14_2)
VG3: R7.1, U$9.55 (P55/IO_L30N_GCLK0_USERCCLK_2)
VG4: R4.1, U$9.56 (P56/IO_L30P_GCLK1_D13_2)
VR0: R17.1, U$9.57 (P57/IO_L14N_D12_2)
VR1: R14.1, U$9.58 (P58/IO_L14P_D11_2)
VR2: R11.1, U$9.59 (P59/IO_L13N_D10_2)
VR3: R8.1, U$9.66 (P66/IO_L2N_CMPMOSI_2)
VR4: R5.1, U$9.67 (P67/IO_L2P_CMPCLK_2)
VSYNC: R1.2, U$9.40 (P40/IO_L64N_D9_2)

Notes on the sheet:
Reserved: NC
0: initial pullups 1: no initial pullups
See http://www.xilinx.com/support/documentation/user_guides/ug380.pdf#page=42 for reference design
To add delay to init_b

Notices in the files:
parts and their libraries:
SparkFun-Aesthetics: Licensing: CC v3.0 Share-Alike You are welcome to use this library for commercial purposes.
